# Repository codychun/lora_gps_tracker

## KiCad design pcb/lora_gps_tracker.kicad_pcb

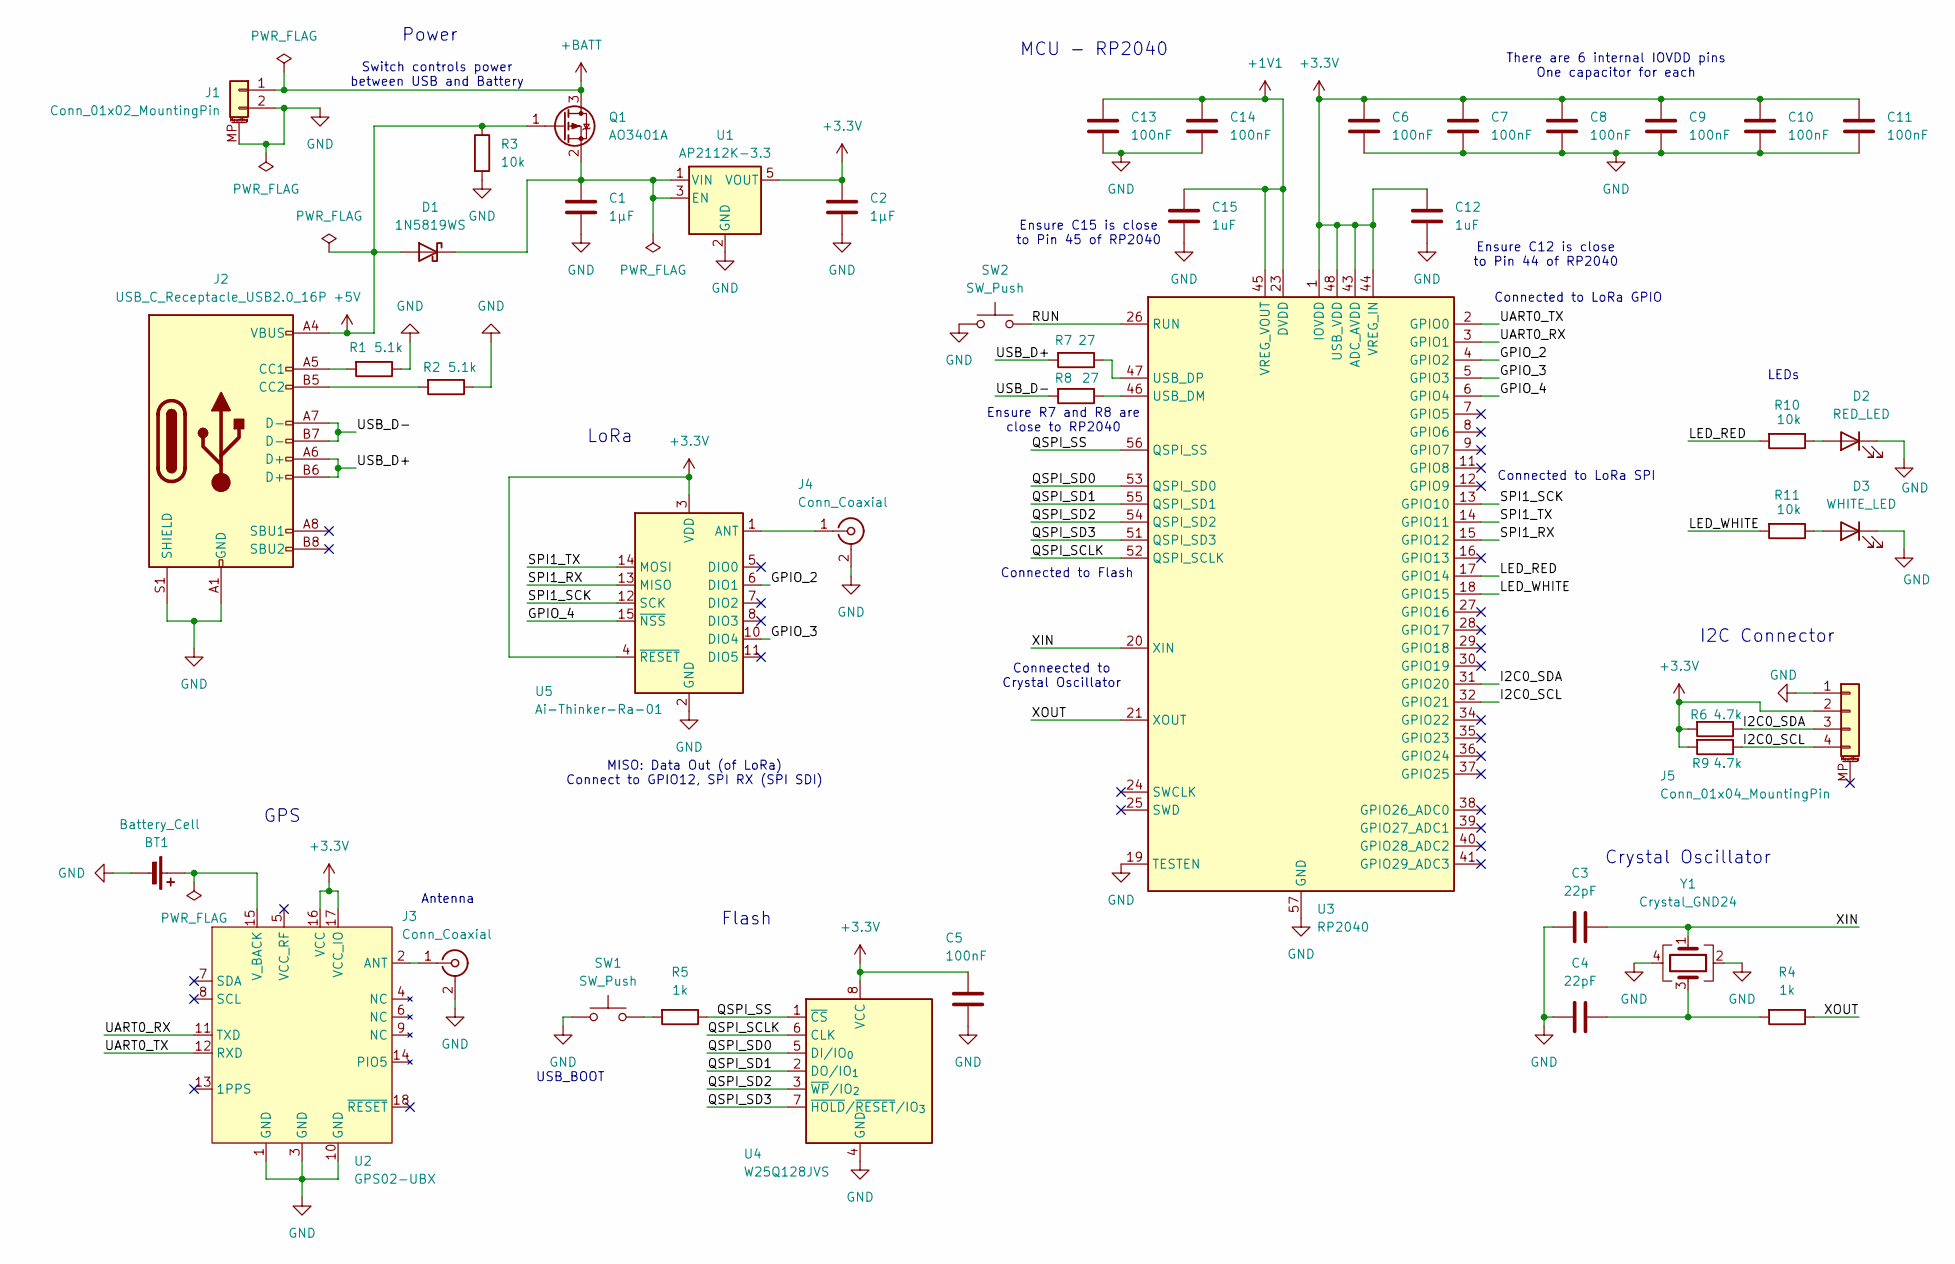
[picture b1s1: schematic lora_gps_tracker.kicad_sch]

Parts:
BT1: Battery_Cell; BatteryHolder_Multicomp_BC-2001_1x2032
C1, C2: 1μF; C_0402_1005Metric
C3, C4: 22pF; C_0402_1005Metric
C5, C6, C7, C8, C9, C10, C11, C13, C14: 100nF; C_0402_1005Metric
C12, C15: 1uF; C_0402_1005Metric
D1: 1N5819WS; D_SOD-323
D2: RED_LED; LED_0603_1608Metric
D3: WHITE_LED; LED_0603_1608Metric
J1: Conn_01x02_MountingPin; JST_PH_S2B-PH-SM4-TB_1x02-1MP_P2.00mm_Horizontal
J2: USB_C_Receptacle_USB2.0_16P; USB_C_Receptacle_HCTL_HC-TYPE-C-16P-01A
J3, J4: Conn_Coaxial; U.FL_Hirose_U.FL-R-SMT-1_Vertical
J5: Conn_01x04_MountingPin; JST_SH_SM04B-SRSS-TB_1x04-1MP_P1.00mm_Horizontal
Q1: AO3401A; SOT-23
R1, R2: 5.1k; R_0402_1005Metric
R3, R10, R11: 10k; R_0402_1005Metric
R4, R5: 1k; R_0402_1005Metric
R6, R9: 4.7k; R_0402_1005Metric
R7, R8: 27; R_0402_1005Metric
SW1, SW2: SW_Push; SW_SPST_SKQG_WithStem
U1: AP2112K-3.3; SOT-23-5
U2: GPS02-UBX; QFN-20_14.5x16.45_Pitch1.8mm
U3: RP2040; QFN-56-1EP_7x7mm_P0.4mm_EP3.2x3.2mm_ThermalVias
U4: W25Q128JVS; SOIC-8_5.3x5.3mm_P1.27mm
U5: Ai-Thinker-Ra-01; Ai-Thinker-Ra-01-LoRa
Y1: Crystal_GND24; Crystal_SMD_3225-4Pin_3.2x2.5mm

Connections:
+1V1: C13.1, C14.1, C15.1, U3.23 (DVDD), U3.45 (VREG_VOUT), U3.50 (DVDD)
+3.3V: C2.1, C5.1, C6.1, C7.1, C8.1, C9.1, C10.1, C11.1, C12.1, J5.2, R6.2, R9.2, U1.5 (VOUT), U2.16 (VCC), U2.17 (VCC_IO), U3.1 (IOVDD), U3.10 (IOVDD), U3.22 (IOVDD), U3.33 (IOVDD), U3.42 (IOVDD), U3.43 (ADC_AVDD), U3.44 (VREG_IN), U3.48 (USB_VDD), U3.49 (IOVDD), U4.8 (VCC), U5.3 (VDD), U5.4 (~RESET)
+5V: D1.2 (A), J2.A4 (VBUS), J2.A9 (VBUS), J2.B4 (VBUS), J2.B9 (VBUS), Q1.1 (G), R3.1
+BATT: J1.1, Q1.3 (D)
/GPIO_2: U3.4 (GPIO2), U5.6 (DIO1)
/GPIO_3: U3.5 (GPIO3), U5.10 (DIO4)
/GPIO_4: U3.6 (GPIO4), U5.15 (~NSS)
/I2C0_SCL: J5.4, R9.1, U3.32 (GPIO21)
/I2C0_SDA: J5.3, R6.1, U3.31 (GPIO20)
/LED_RED: R10.2, U3.17 (GPIO14)
/LED_WHITE: R11.2, U3.18 (GPIO15)
/QSPI_SCLK: U3.52 (QSPI_SCLK), U4.6 (CLK)
/QSPI_SD0: U3.53 (QSPI_SD0), U4.5 (DI/IO_{0})
/QSPI_SD1: U3.55 (QSPI_SD1), U4.2 (DO/IO_{1})
/QSPI_SD2: U3.54 (QSPI_SD2), U4.3 (~WP/IO_{2})
/QSPI_SD3: U3.51 (QSPI_SD3), U4.7 (~HOLD/~RESET/IO_{3})
/QSPI_SS: R5.1, U3.56 (QSPI_SS), U4.1 (~CS)
/RUN: SW2.2, U3.26 (RUN)
/SPI1_RX: U3.15 (GPIO12), U5.13 (MISO)
/SPI1_SCK: U3.13 (GPIO10), U5.12 (SCK)
/SPI1_TX: U3.14 (GPIO11), U5.14 (MOSI)
/UART0_RX: U2.11 (TXD), U3.3 (GPIO1)
/UART0_TX: U2.12 (RXD), U3.2 (GPIO0)
/USB_D+: J2.A6 (D+), J2.B6 (D+), R7.2
/USB_D-: J2.A7 (D-), J2.B7 (D-), R8.2
/XIN: C3.1, U3.20 (XIN), Y1.1
/XOUT: R4.1, U3.21 (XOUT)
GND: BT1.2 (-), C1.2, C2.2, C3.2, C4.2, C5.2, C6.2, C7.2, C8.2, C9.2, C10.2, C11.2, C12.2, C13.2, C14.2, C15.2, D2.1 (K), D3.1 (K), J1.2, J1.MP (MountPin), J2.A1 (GND), J2.A12 (GND), J2.B1 (GND), J2.B12 (GND), J2.S1 (SHIELD), J3.2 (Ext), J4.2 (Ext), J5.1, R1.1, R2.1, R3.2, SW1.1, SW2.1, U1.2 (GND), U2.1 (GND), U2.3 (GND), U2.10 (GND), U3.19 (TESTEN), U3.57 (GND), U4.4 (GND), U5.2 (GND), U5.9 (GND), U5.16 (GND), Y1.2, Y1.4
unnamed: BT1.1 (+), U2.15 (V_BACK)
unnamed: C4.1, R4.2, Y1.3
unnamed: C1.1, D1.1 (K), Q1.2 (S), U1.1 (VIN), U1.3 (EN)
unnamed: D2.2 (A), R10.1
unnamed: D3.2 (A), R11.1
unnamed: J2.A5 (CC1), R1.2
unnamed: J2.B5 (CC2), R2.2
unnamed: J3.1 (In), U2.2 (ANT)
unnamed: J4.1 (In), U5.1 (ANT)
unnamed: R5.2, SW1.2
unnamed: R8.1, U3.46 (USB_DM)
unnamed: R7.1, U3.47 (USB_DP)

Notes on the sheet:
Conneected to Crystal Oscillator
Power
MISO: Data Out (of LoRa) Connect to GPIO12, SPI RX (SPI SDI)
There are 6 internal IOVDD pins One capacitor for each
USB_BOOT
I2C Connector
LoRa
MCU - RP2040
Flash
Connected to LoRa SPI
LEDs
Ensure C15 is close to Pin 45 of RP2040
Switch controls power between USB and Battery
Connected to LoRa GPIO
Antenna
Ensure C12 is close to Pin 44 of RP2040
Connected to Flash
Ensure R7 and R8 are close to RP2040
Crystal Oscillator
GPS

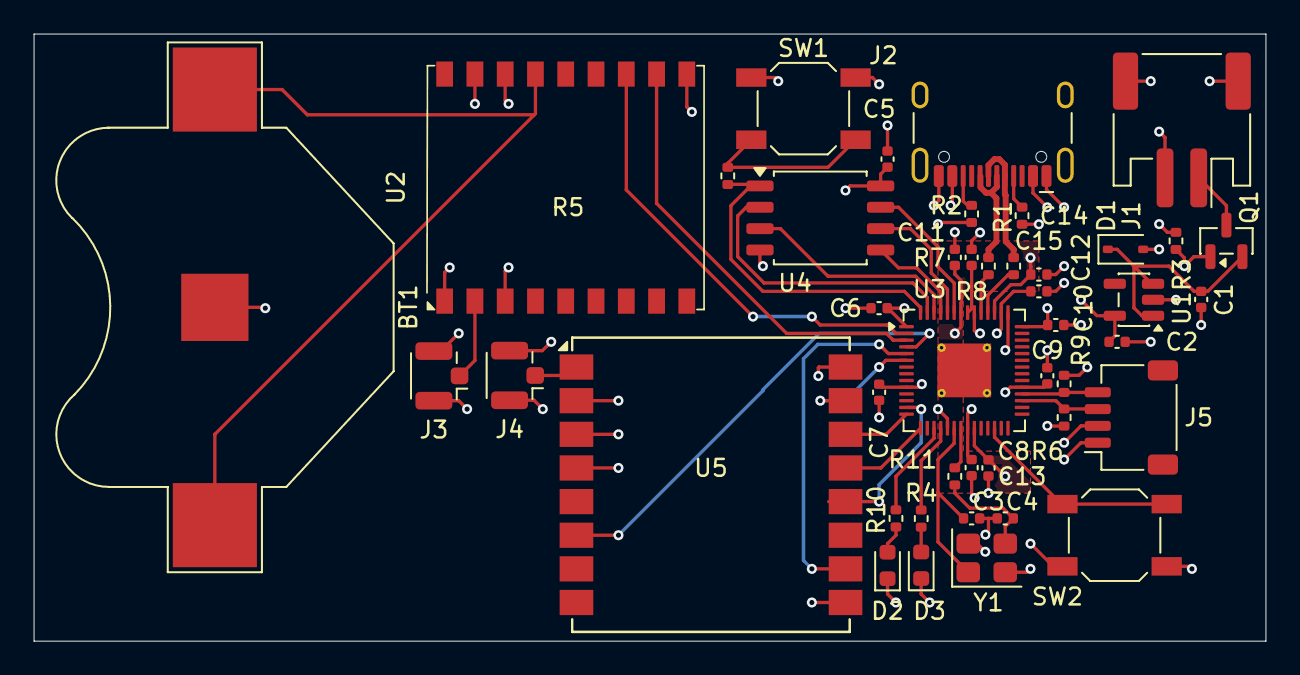
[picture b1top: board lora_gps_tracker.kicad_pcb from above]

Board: 4 copper layers, 73.2 x 36.1 mm, 44 parts (0 on the bottom side), 40 nets.

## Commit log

2026-06-26 Removed duplicates
